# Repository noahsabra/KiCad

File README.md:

# KiCad
Keyboard PCB Designs Done through KiCad

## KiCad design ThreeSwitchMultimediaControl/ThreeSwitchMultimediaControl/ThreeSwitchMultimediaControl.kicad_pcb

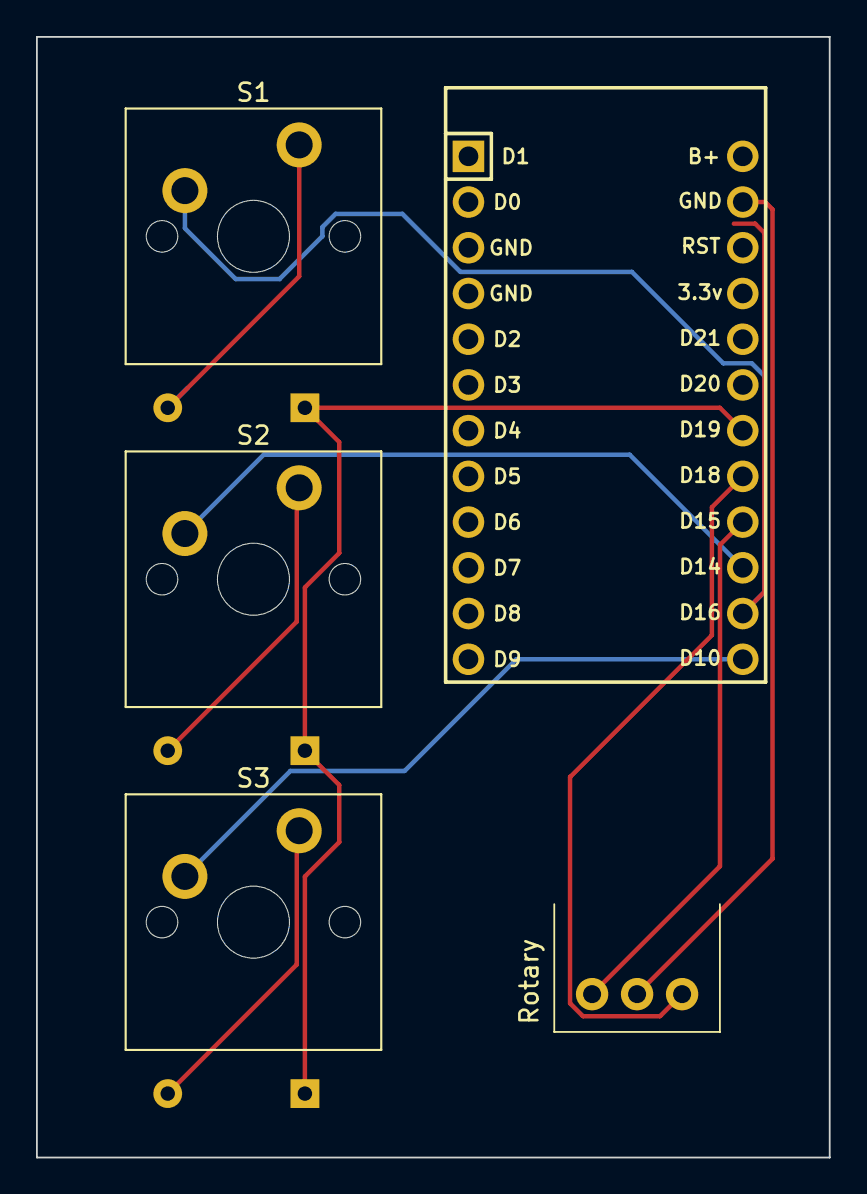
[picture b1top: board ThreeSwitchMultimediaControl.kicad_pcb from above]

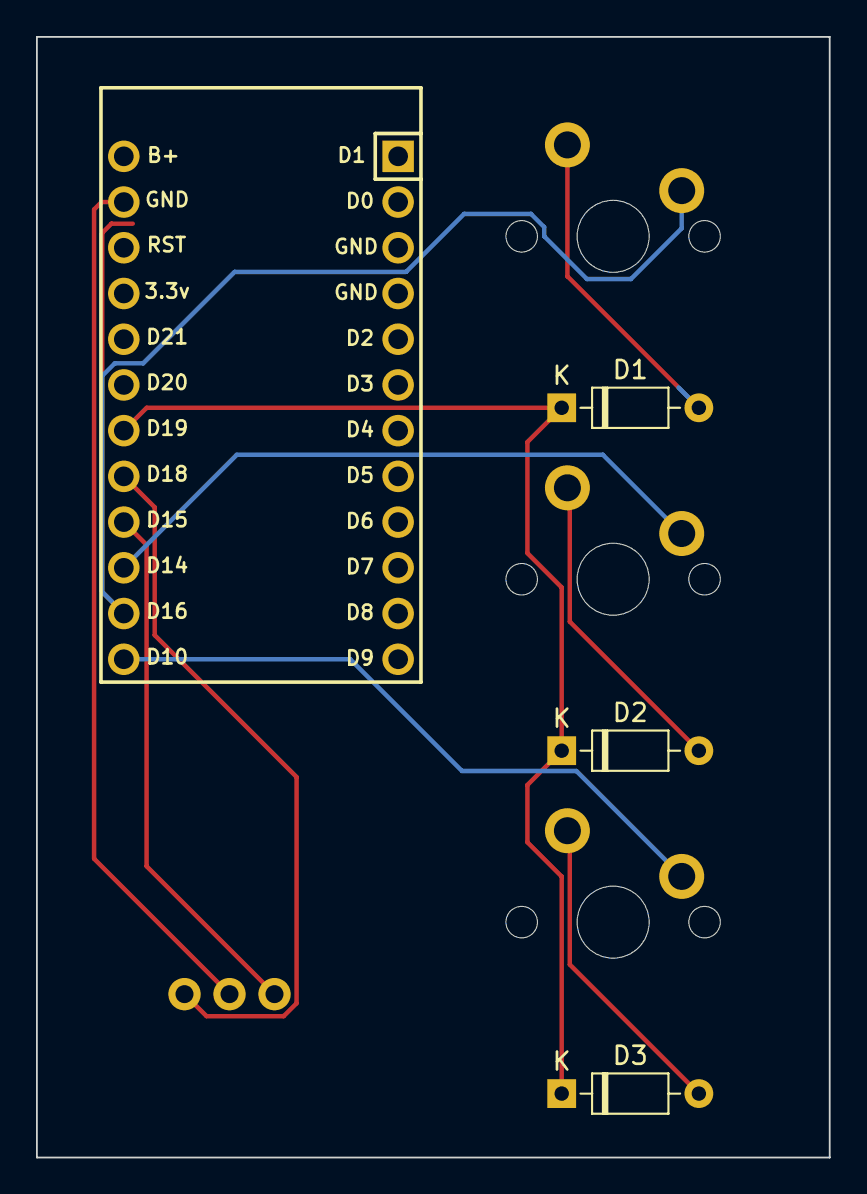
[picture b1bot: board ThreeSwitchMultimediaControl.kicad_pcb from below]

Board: 2 copper layers, 44.0 x 62.3 mm, 8 parts (3 on the bottom side), 10 nets.

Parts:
D1, D2, D3: Diode; Diode_DO-35
Rotary: RotaryEncoder; RotaryEncoder_Bourns_Horizontal_PEC09-2xxxF-Nxxxx
S1, S2, S3: Keyswitch; MX_PCB_1.00u
U1: Nice_Nano_V2

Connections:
unnamed: D1.2 (A), S1.2
unnamed: D1.1 (K), D2.1 (K), D3.1 (K), U1.18 (D19)
unnamed: D2.2 (A), S2.2
unnamed: D3.2 (A), S3.2
unnamed: Rotary.C, U1.23 (GND)
unnamed: S3.1, U1.13 (D10)
unnamed: S2.1, U1.15 (D14)
unnamed: Rotary.B, U1.16 (D15)
unnamed: S1.1, U1.14 (D16)
unnamed: Rotary.A, U1.17 (D18)

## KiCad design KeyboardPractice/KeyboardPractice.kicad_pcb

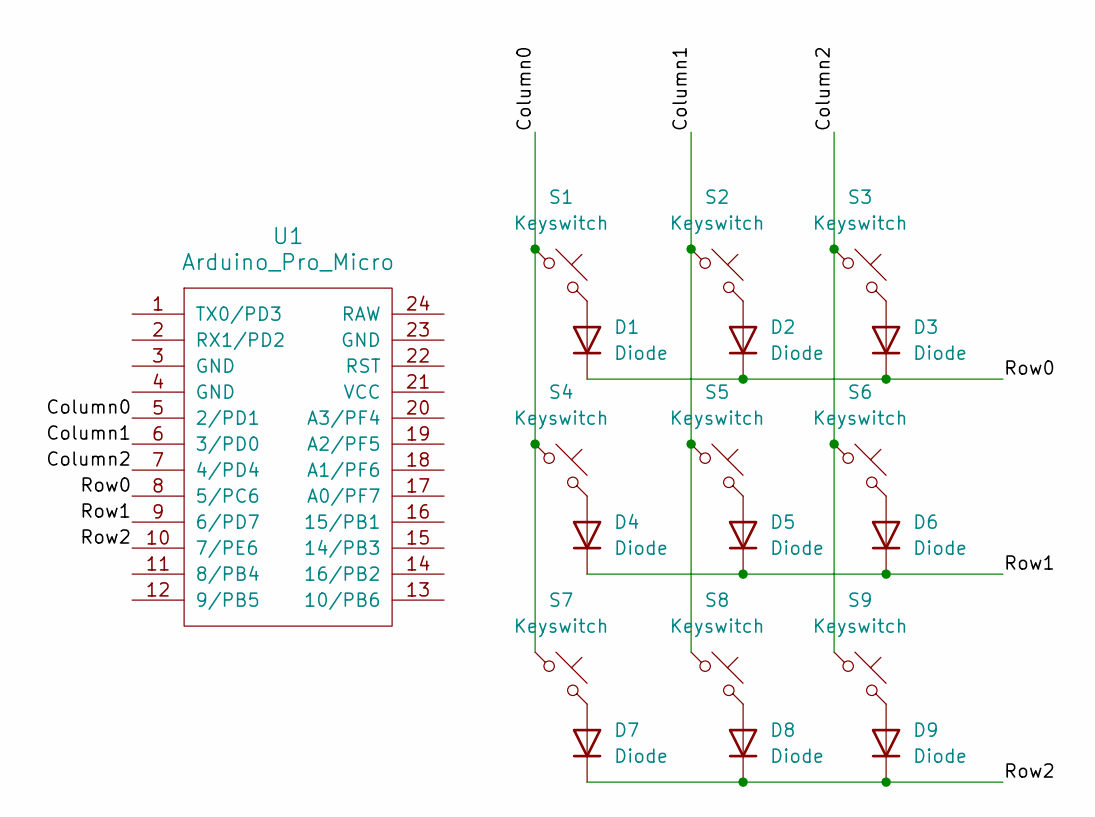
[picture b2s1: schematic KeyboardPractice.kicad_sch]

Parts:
D1, D2, D3, D4, D5, D6, D7, D8, D9: Diode; Diode_DO-35
S1, S2, S3, S4, S5, S6, S7, S8, S9: Keyswitch; MX_PCB_1.00u
U1: Arduino_Pro_Micro

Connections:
/Column0: S1.1, S4.1, S7.1, U1.5 (2/PD1)
/Column1: S2.1, S5.1, S8.1, U1.6 (3/PD0)
/Column2: S3.1, S6.1, S9.1, U1.7 (4/PD4)
/Row0: D1.1 (K), D2.1 (K), D3.1 (K), U1.8 (5/PC6)
/Row1: D4.1 (K), D5.1 (K), D6.1 (K), U1.9 (6/PD7)
/Row2: D7.1 (K), D8.1 (K), D9.1 (K), U1.10 (7/PE6)
unnamed: D1.2 (A), S1.2
unnamed: D2.2 (A), S2.2
unnamed: D3.2 (A), S3.2
unnamed: D4.2 (A), S4.2
unnamed: D5.2 (A), S5.2
unnamed: D6.2 (A), S6.2
unnamed: D7.2 (A), S7.2
unnamed: D8.2 (A), S8.2
unnamed: D9.2 (A), S9.2

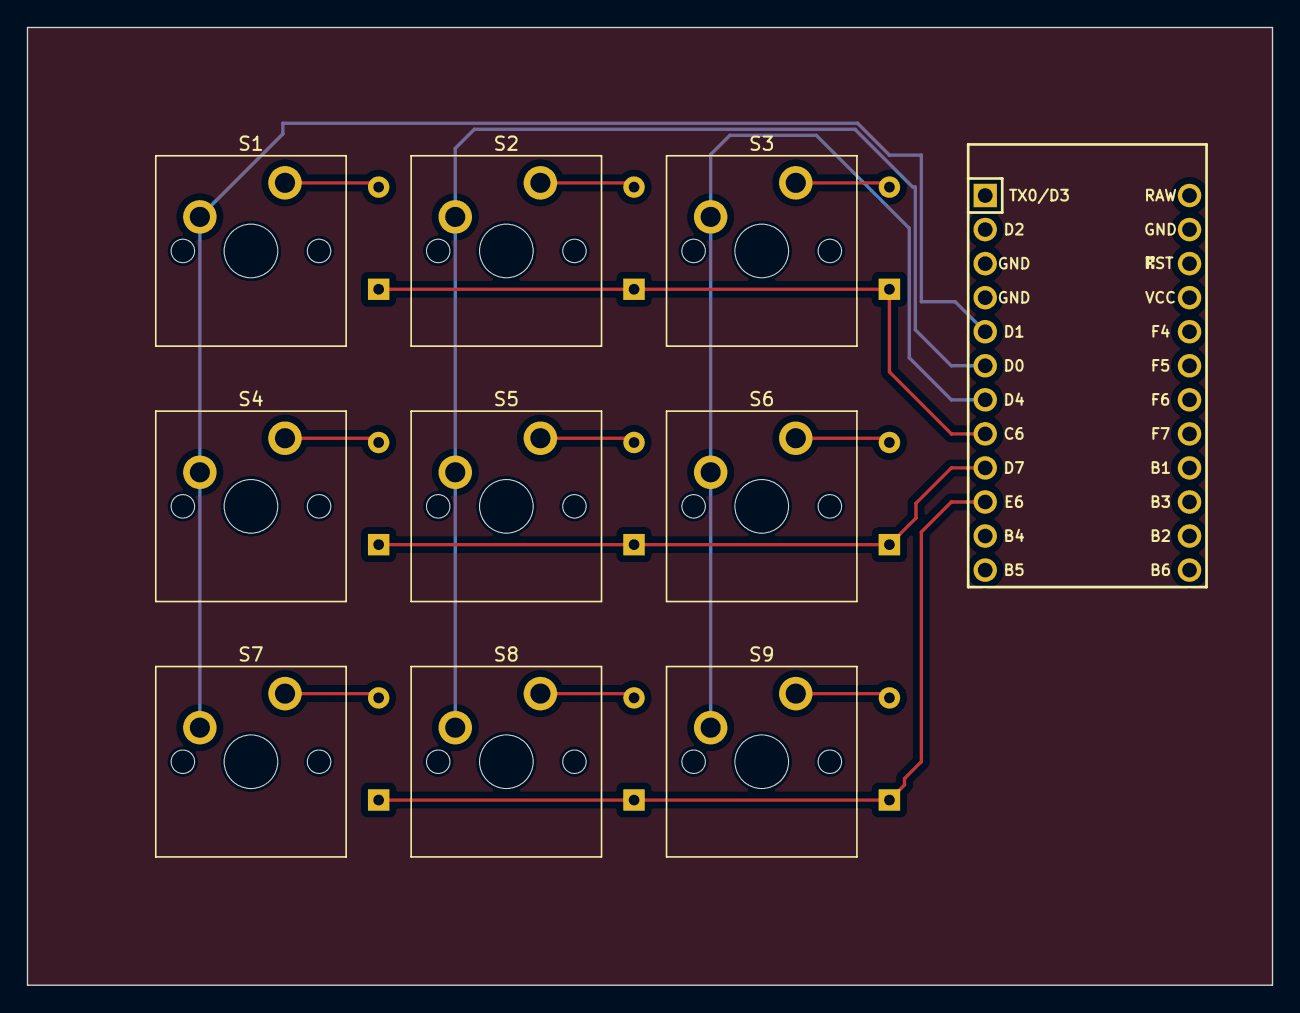
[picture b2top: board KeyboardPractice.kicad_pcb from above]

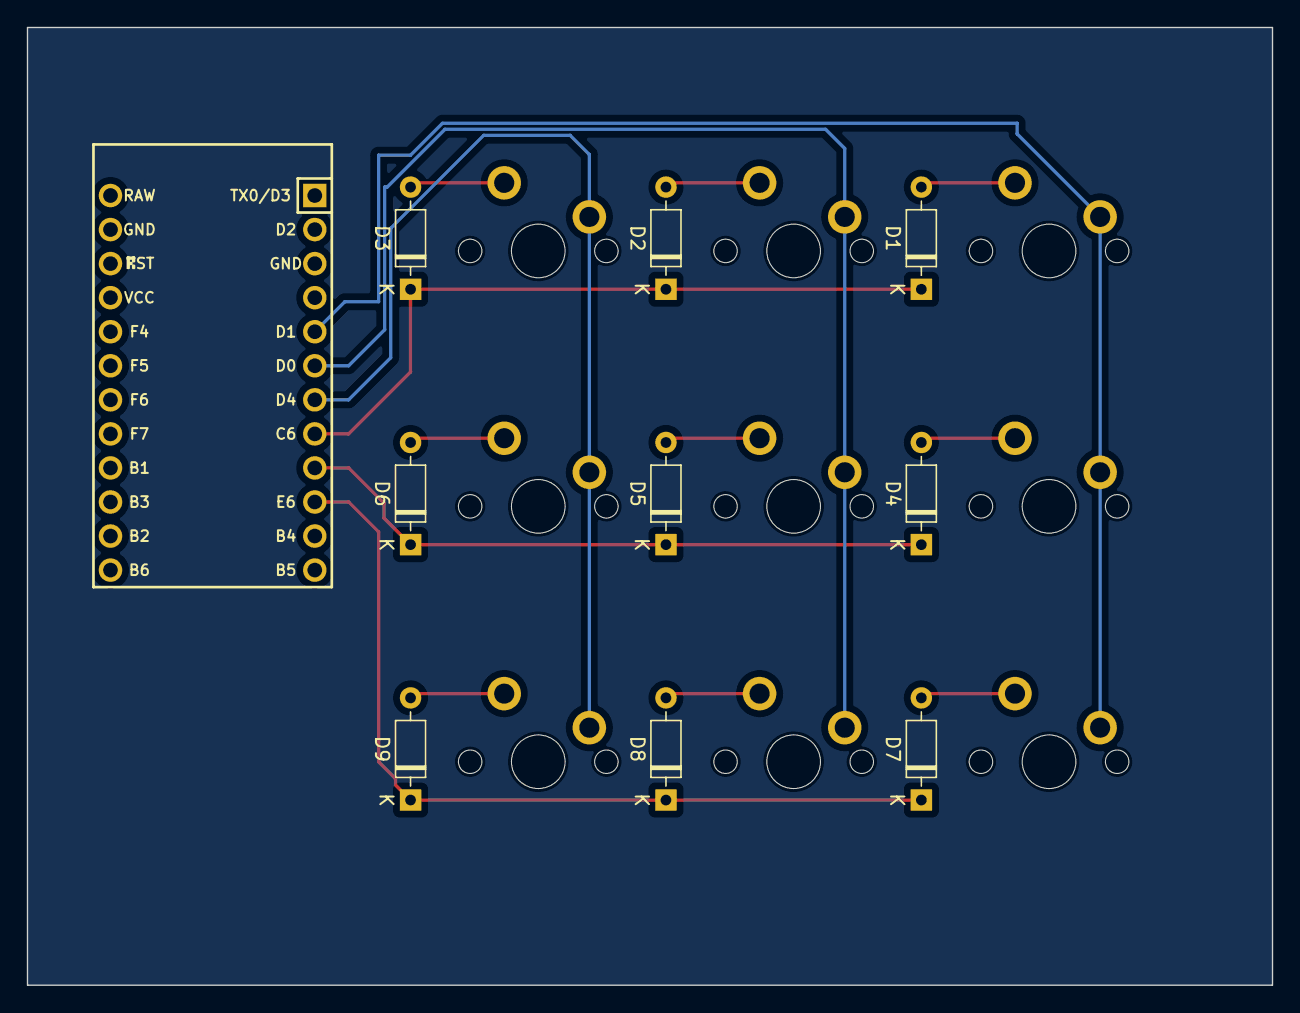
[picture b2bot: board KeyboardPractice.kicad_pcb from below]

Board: 2 copper layers, 92.9 x 71.4 mm, 19 parts (9 on the bottom side), 15 nets.

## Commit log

2024-02-22 Three Switch Multimedia Control
    Multimedia Controller intended for Skip, Play/Pause, and Go Back, as well as including a rotary encoder for Volume Control. Work In Progress
2024-02-24 Three Switch Multimedia Control with Rotary Knob
